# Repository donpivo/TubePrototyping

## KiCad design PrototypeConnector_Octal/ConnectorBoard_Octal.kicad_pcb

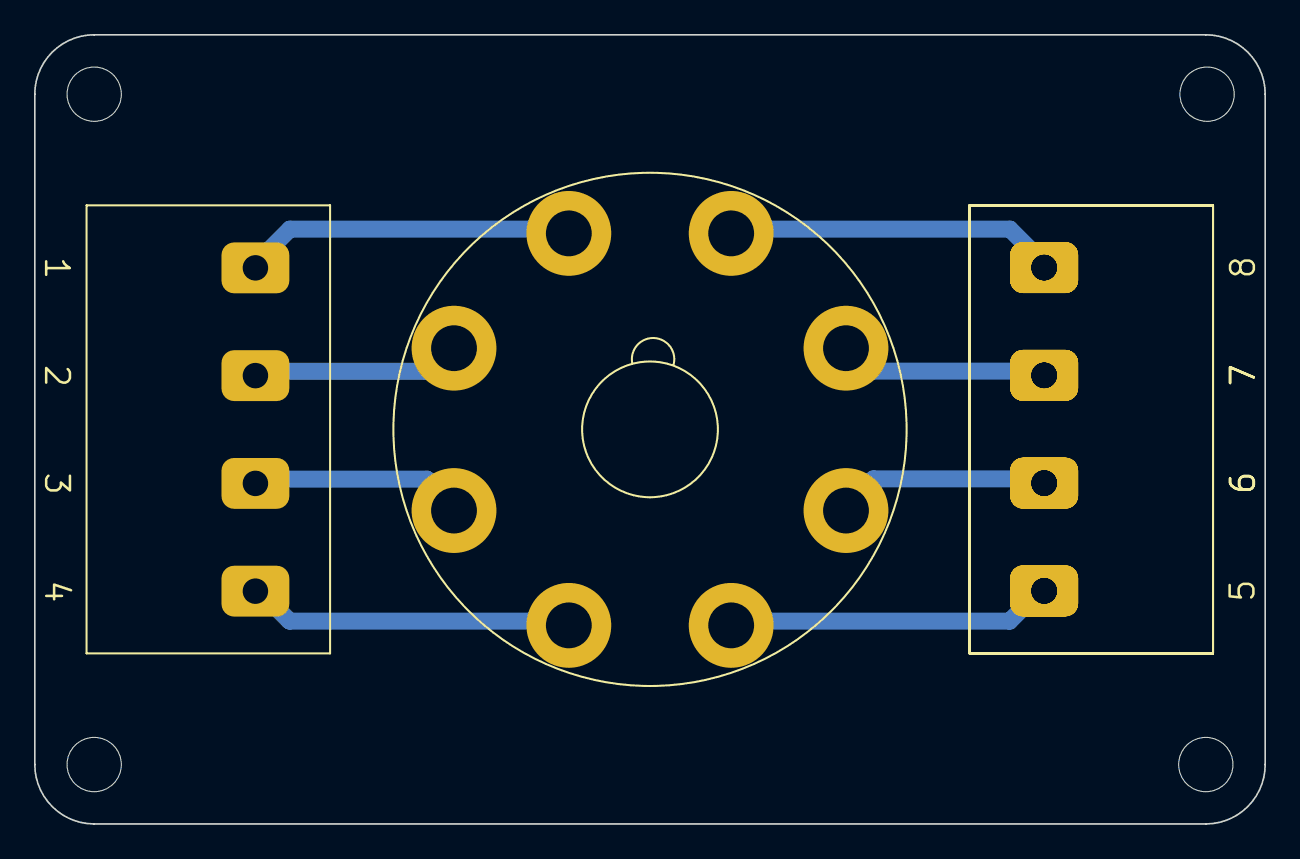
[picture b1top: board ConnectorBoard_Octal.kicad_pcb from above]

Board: 2 copper layers, 72.5 x 46.5 mm, 9 parts (0 on the bottom side), 8 nets.

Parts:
H1, H2, H3, H4: MountingHole; MountingHole_3.2mm_M3
J1: Octal Socket; Octal_Ceramic
J2, J3, J3#2, J3#3: ScrewTerminal; ScrewTerminal_JL635_4

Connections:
unnamed: J1.1, J2.1
unnamed: J1.2, J2.2
unnamed: J1.3, J2.3
unnamed: J1.4, J2.4
unnamed: J1.5, J3.1, J3#2.1, J3#3.1
unnamed: J1.6, J3.2, J3#2.2, J3#3.2
unnamed: J1.7, J3.3, J3#2.3, J3#3.3
unnamed: J1.8, J3.4, J3#2.4, J3#3.4

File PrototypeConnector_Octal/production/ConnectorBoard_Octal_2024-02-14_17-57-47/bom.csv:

Designator,Footprint,Quantity,Value,LCSC Part #
"H1, H2, H3, H4",MountingHole_3.2mm_M3,4,MountingHole,
J1,Octal_Ceramic,1,Octal Socket,
"J2, J3_3, J3_2, J3",ScrewTerminal_JL635_4,4,ScrewTerminal,

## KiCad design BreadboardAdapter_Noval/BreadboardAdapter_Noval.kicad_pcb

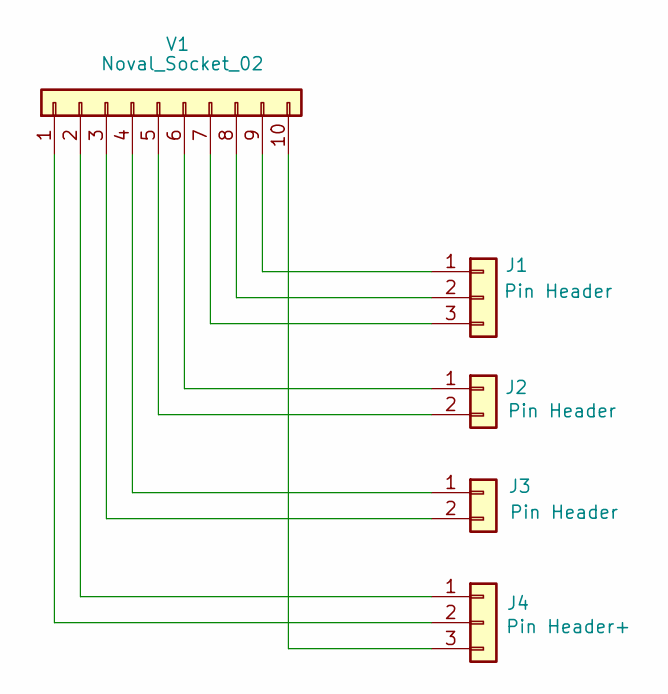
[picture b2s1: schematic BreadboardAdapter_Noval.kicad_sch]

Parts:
J1: Pin Header; PinHeader_1x03_P5.08mm_Vertical
J2, J3: Pin Header; PinHeader_1x02_P5.08mm_Vertical
J4: Pin Header+; PinHeader_1x03_P5.08mm_Vertical
V1: Noval_Socket_02; NovalSocket_Ceramic_1

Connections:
unnamed: J1.1, V1.9
unnamed: J1.2, V1.8
unnamed: J1.3, V1.7
unnamed: J2.1, V1.6
unnamed: J2.2, V1.5
unnamed: J3.1, V1.4
unnamed: J3.2, V1.3
unnamed: J4.1, V1.2
unnamed: J4.2, V1.1
unnamed: J4.3, V1.10

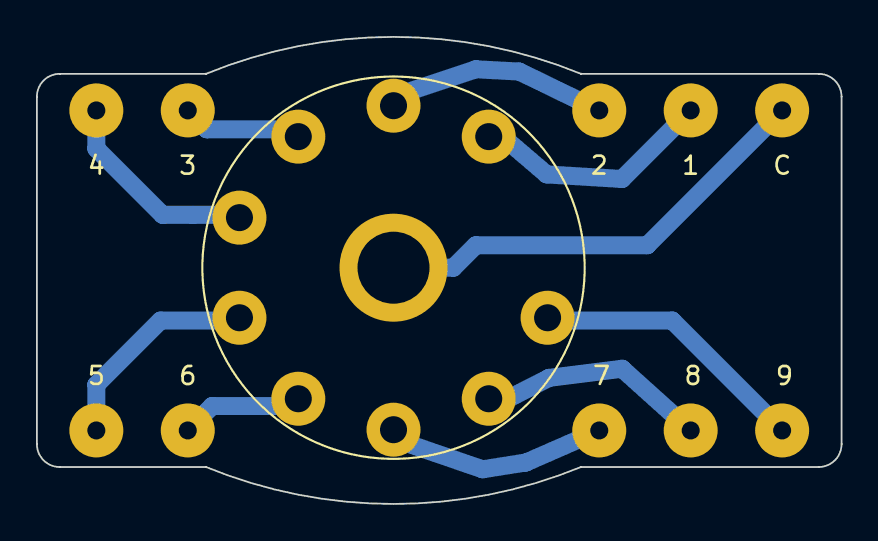
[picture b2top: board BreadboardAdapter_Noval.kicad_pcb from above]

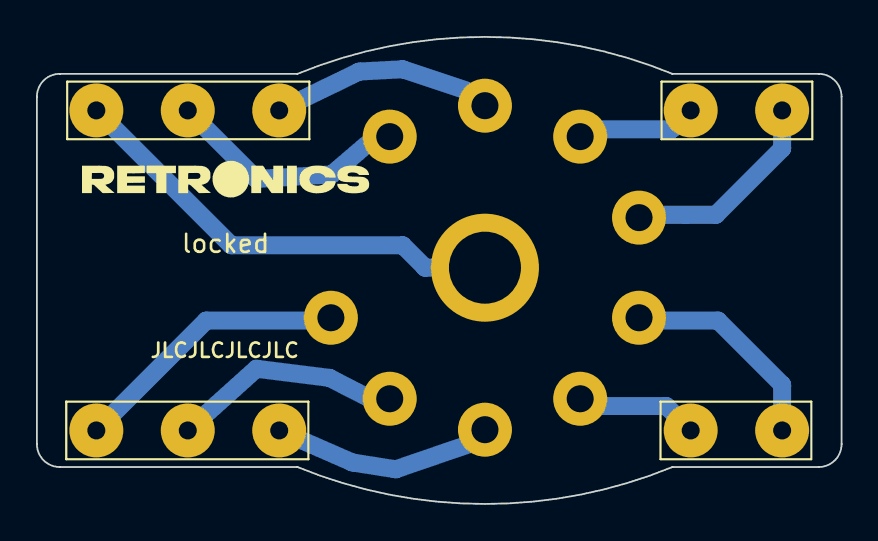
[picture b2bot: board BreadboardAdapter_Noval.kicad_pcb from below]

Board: 2 copper layers, 44.7 x 25.9 mm, 5 parts (4 on the bottom side), 10 nets.

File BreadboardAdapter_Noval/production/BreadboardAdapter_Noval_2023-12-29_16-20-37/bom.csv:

Designator,Footprint,Quantity,Value,LCSC Part #
J1,PinHeader_1x03_P5.08mm_Vertical,1,Pin Header,
"J2, J3",PinHeader_1x02_P5.08mm_Vertical,2,Pin Header,
J4,PinHeader_1x03_P5.08mm_Vertical,1,Pin Header+,
V1,NovalSocket_Ceramic_1,1,Noval_Socket_02,

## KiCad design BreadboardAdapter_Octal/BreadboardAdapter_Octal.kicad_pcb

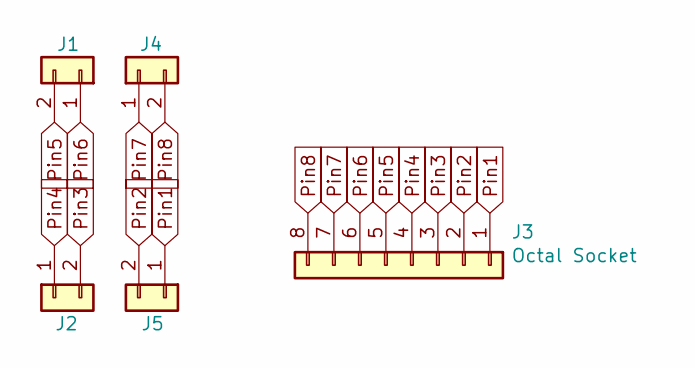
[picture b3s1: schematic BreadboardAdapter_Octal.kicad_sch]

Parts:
J1, J2, J4, J5: Conn_01x02; PinHeader_1x02_P5.08mm_Vertical
J3: Octal Socket; Octal_Ceramic

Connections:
Pin1: J3.1, J5.1
Pin2: J3.2, J5.2
Pin3: J2.2, J3.3
Pin4: J2.1, J3.4
Pin5: J1.2, J3.5
Pin6: J1.1, J3.6
Pin7: J3.7, J4.1
Pin8: J3.8, J4.2

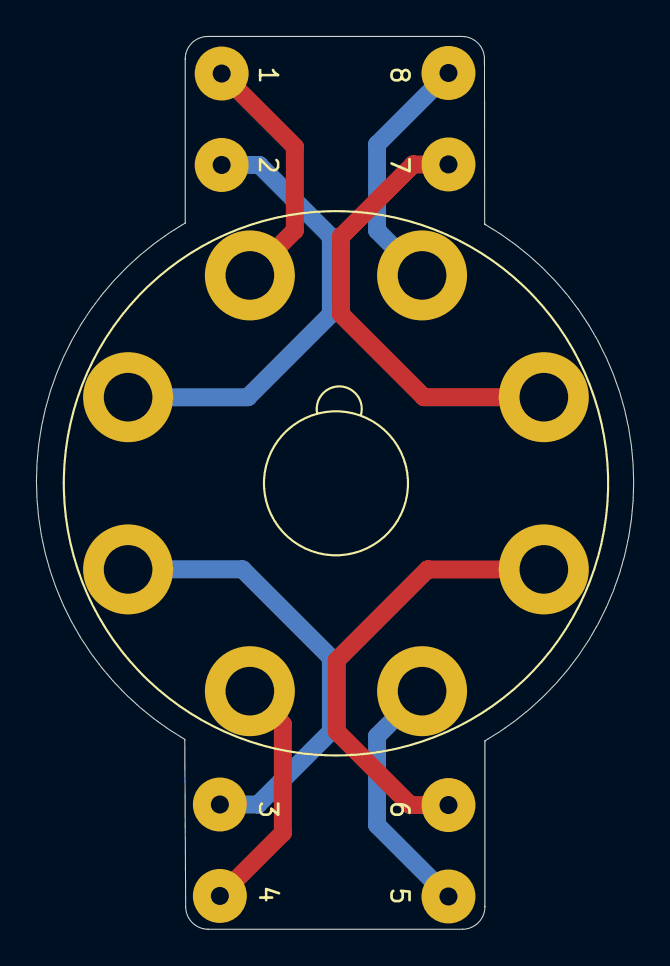
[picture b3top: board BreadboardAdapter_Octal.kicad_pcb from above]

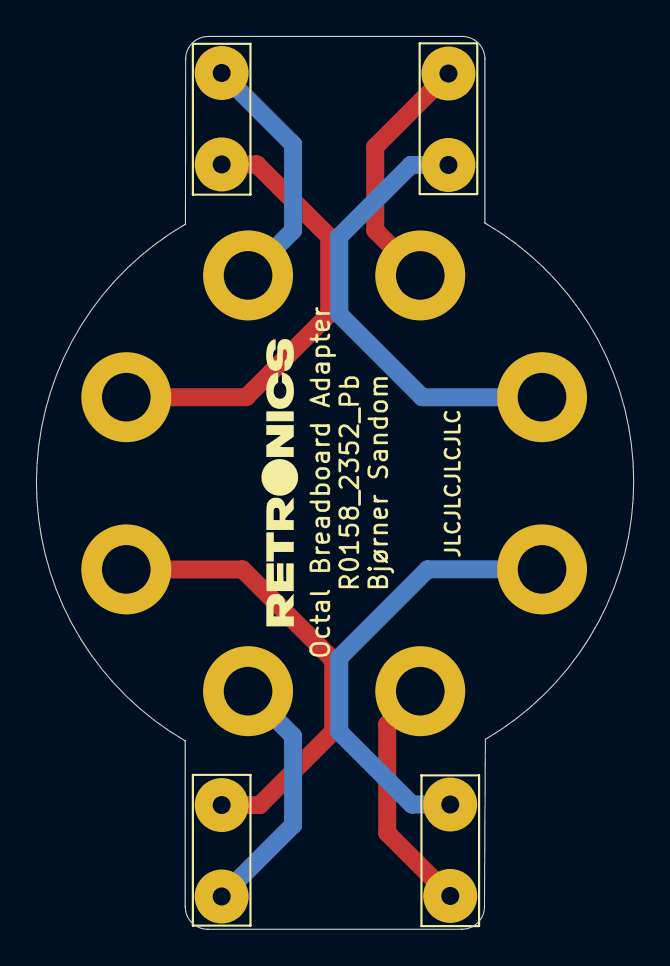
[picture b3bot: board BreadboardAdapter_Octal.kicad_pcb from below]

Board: 2 copper layers, 33.2 x 49.6 mm, 5 parts (4 on the bottom side), 8 nets.

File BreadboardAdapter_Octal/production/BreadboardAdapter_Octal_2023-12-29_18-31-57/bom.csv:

Designator,Footprint,Quantity,Value,LCSC Part #
"J1, J2, J4, J5",PinHeader_1x02_P5.08mm_Vertical,4,Conn_01x02,
J3,Octal_Ceramic,1,Conn_01x08,
